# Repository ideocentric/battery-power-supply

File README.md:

# battery-power-supply
The purpose of this project is to have a rechargeable battery intended to be inside an enclosure for various synthesizer designs, however, it can be utilized for any purpose.

The motivation for this project was that I have not found an adequate solution.  There are a number of current solutions available, but the following limitations create issues for the overall design.

1.  Soldered on USB charging ports
2.  Soldered on power switch
3.  Soldered on power, charging and charge LEDs

Due to the above, they do not suite the usage inside of a project enclosure without desoldering these components and attaching wires in their place for panel mount switches, power and LEDs.

I have, however, found one solution that satisfied the above issues.  Unfortunately, these devices produced audible frequencies that prevented it being functional as a power supply for a sythesizer.

Due to the above conditions, I reached out to work with an engineer to help create the schematic and PCB layout for this purpose.  

The devise is intended to be used with 2 18650 batteries.  The JST connectors are provided to hook up the components such as the DC Barrel Jack for charging, 5v output for the device, Power switch and LEDs for Power, Charging and Charged status indicators.

The power supply should be 5v2a (or 5v3a).  Output is 5v1a.

I had the device manufactured at https://jlcpcb.com of which all components are normal stock items.

# Known Issues:
The current solution does not provide protection for low or short battery (perhaps this will be modified in a future version).

The status light output of the CN3302 IC is a little vague in it’s output as both lights appear to be on during charging.

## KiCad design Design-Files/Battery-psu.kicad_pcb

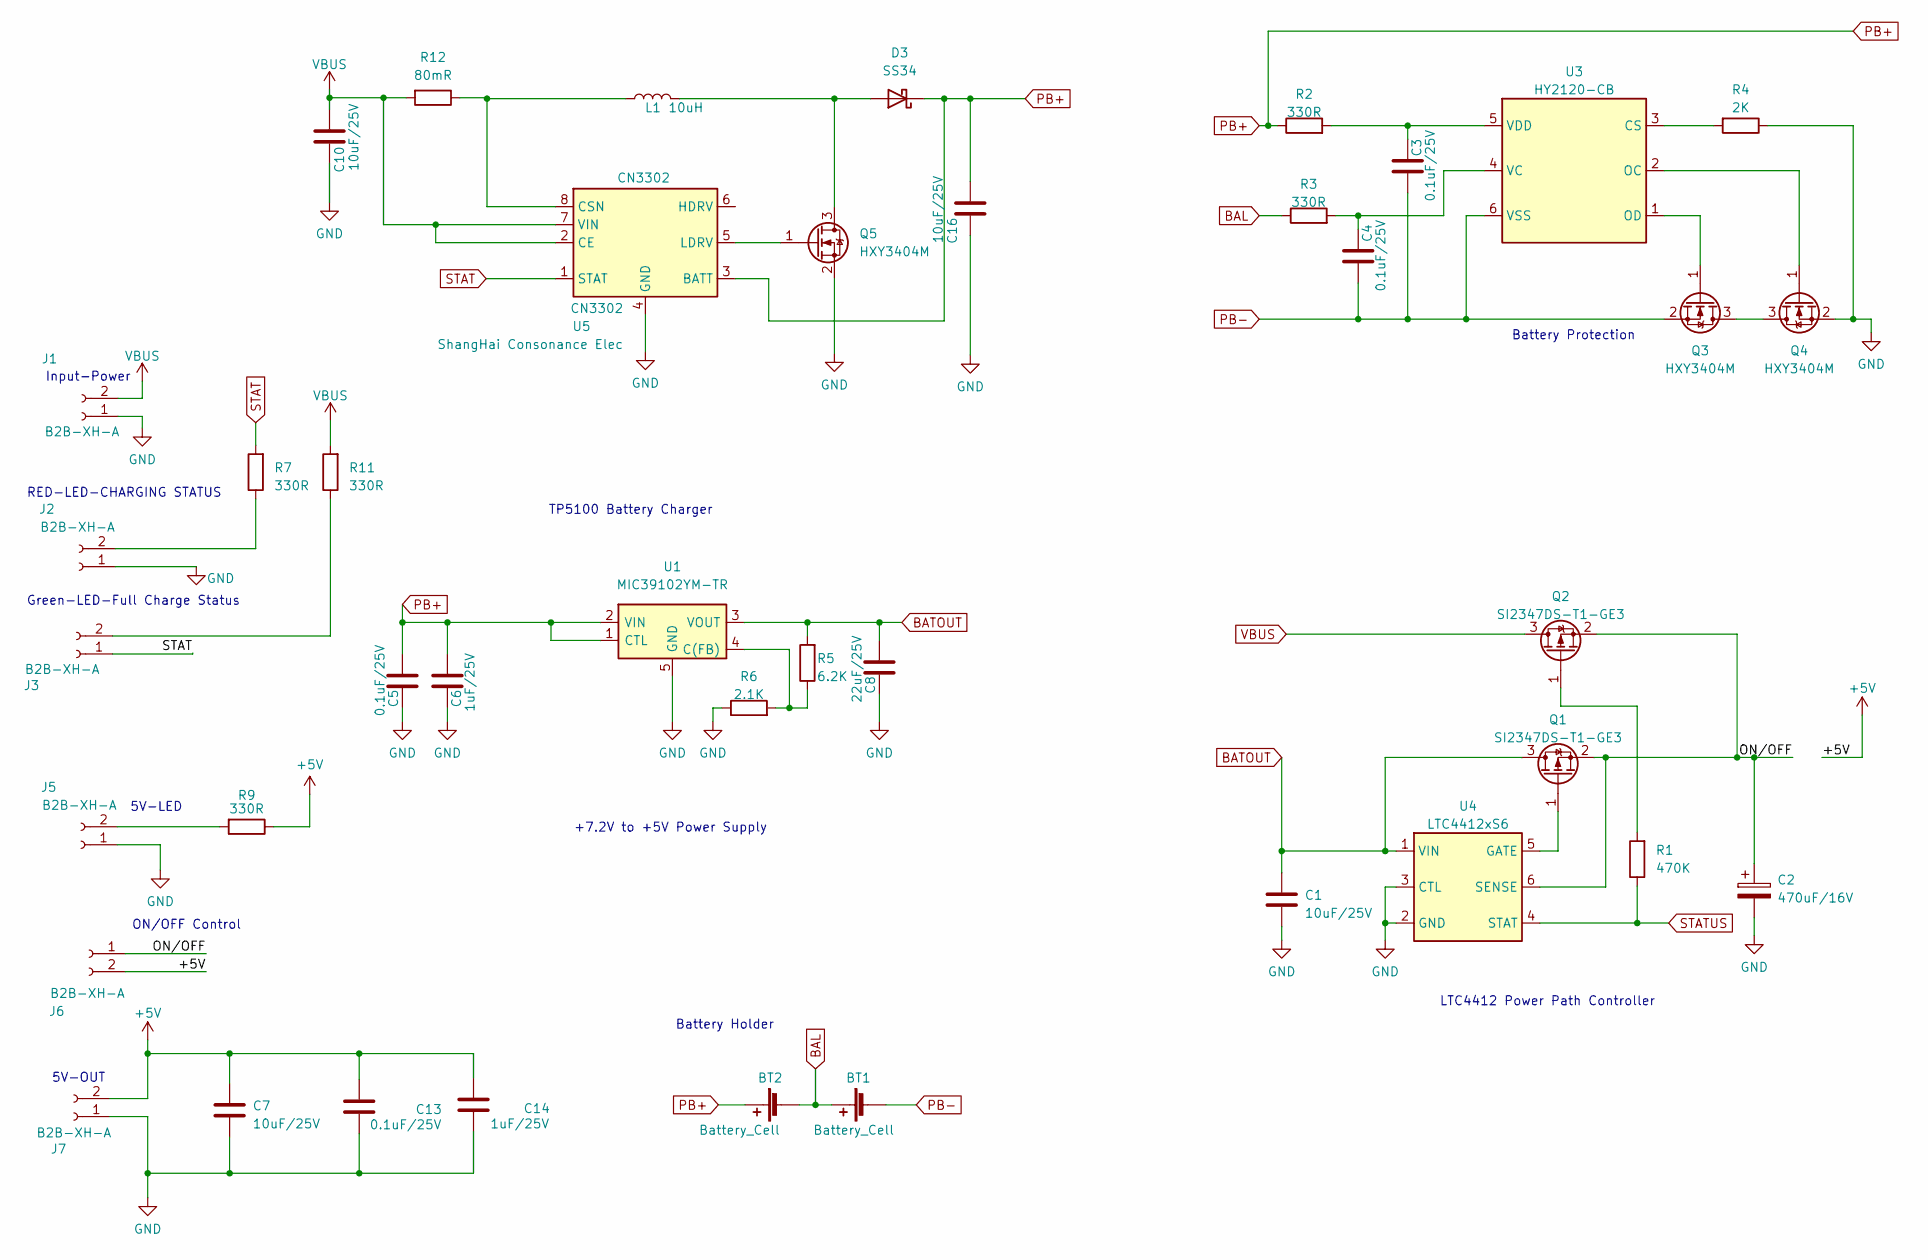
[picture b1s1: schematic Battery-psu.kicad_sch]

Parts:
BT1: Battery_Cell; BatteryHolder_MPD_BH-18650-PC2; LCSC-PN C19184083
BT2: Battery_Cell; BatteryHolder_MPD_BH-18650-PC2; LCSC PN C19184083
C1, C7, C10, C16: 10uF/25V; C_0603_1608Metric; LCSC PN C96446
C2: 470uF/16V; CP_Elec_6.3x7.7; LCSC PN C87858
C3, C4, C5, C13: 0.1uF/25V; C_0603_1608Metric; LCSC PN C83054
C6, C14: 1uF/25V; C_0603_1608Metric; LCSC PN C2857985
C8: 22uF/25V; C_0603_1608Metric; LCSC PN C602037
D3: SS34; D_SMA; LCSC PN C3011102
J1, J2, J3, J5, J6, J7: B2B-XH-A; JST_XH_B2B-XH-A_1x02_P2.50mm_Vertical; LCSC PN C158012
L1: 10uH; L_Wuerth_HCI-1040; LCSC PN C182194
Q1, Q2: SI2347DS-T1-GE3; SOT-23; LCSC PN C145002
Q3, Q4, Q5: HXY3404M; SOT-23; LCSC PN C2926128
R1: 470K; R_0603_1608Metric; LCSC PN C2907171
R2, R3, R7, R9, R11: 330R; R_0603_1608Metric; LCSC PN C2907152
R4: 2K; R_0603_1608Metric; LCSC PN C2907137
R5: 6.2K; R_0603_1608Metric; LCSC PN C2907054
R6: 2.1K; R_0603_1608Metric; LCSC PN C2907137
R12: 80mR; R_2512_6332Metric; LCSC PN C421509
U1: MIC39102YM-TR; SOIC-8_3.9x4.9mm_P1.27mm; LCSC PN C627993
U3: HY2120-CB; SOT-23-6; LCSC PN C116509
U4: LTC4412xS6; TSOT-23-6; LCSC PN C514442
U5: CN3302; SOIC-8_3.9x4.9mm_P1.27mm; LCSC PN C559039

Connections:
+5V: C7.1, C13.1, C14.1, J6.2, J7.2, R9.1
/ON/OFF: C2.1, J6.1, Q1.2 (S), Q2.2 (S), U4.6 (SENSE)
BAL: BT1.1 (+), BT2.2 (-), R3.1
BATOUT: C1.1, C8.1, Q1.3 (D), R5.2, U1.3 (VOUT), U4.1 (VIN)
GND: C1.2, C2.2, C5.2, C6.2, C7.2, C8.2, C10.2, C13.2, C14.2, C16.2, J1.1, J2.1, J5.1, J7.1, Q4.2 (S), Q5.2 (S), R4.1, R6.1, U1.5 (GND), U1.6 (GND), U1.7 (GND), U1.8 (GND), U4.2 (GND), U4.3 (CTL), U5.4 (GND)
unnamed: D3.2 (A), L1.2, Q5.3 (D)
unnamed: J2.2, R7.1
unnamed: J3.2, R11.1
unnamed: J5.2, R9.2
unnamed: Q1.1 (G), U4.5 (GATE)
unnamed: Q2.1 (G), R1.2
unnamed: Q3.3 (D), Q4.3 (D)
unnamed: Q3.1 (G), U3.1 (OD)
unnamed: Q4.1 (G), U3.2 (OC)
unnamed: Q5.1 (G), U5.5 (LDRV)
unnamed: R5.1, R6.2, U1.4 (C(FB))
unnamed: R4.2, U3.3 (CS)
unnamed: C4.1, R3.2, U3.4 (VC)
unnamed: C3.1, R2.2, U3.5 (VDD)
unnamed: L1.1, R12.1, U5.8 (CSN)
PB+: BT2.1 (+), C5.1, C6.1, C16.1, D3.1 (K), R2.1, U1.1 (CTL), U1.2 (VIN), U5.3 (BATT)
PB-: BT1.2 (-), C3.2, C4.2, Q3.2 (S), U3.6 (VSS)
STAT: J3.1, R7.2, U5.1 (STAT)
STATUS: R1.1, U4.4 (STAT)
VBUS: C10.1, J1.2, Q2.3 (D), R11.2, R12.2, U5.2 (CE), U5.7 (VIN)

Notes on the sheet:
ON/OFF Control
Battery Holder
5V-LED
+7.2V to +5V Power Supply
5V-OUT
LTC4412 Power Path Controller
RED-LED-CHARGING STATUS
Battery Protection
TP5100 Battery Charger
Green-LED-Full Charge Status
Input-Power

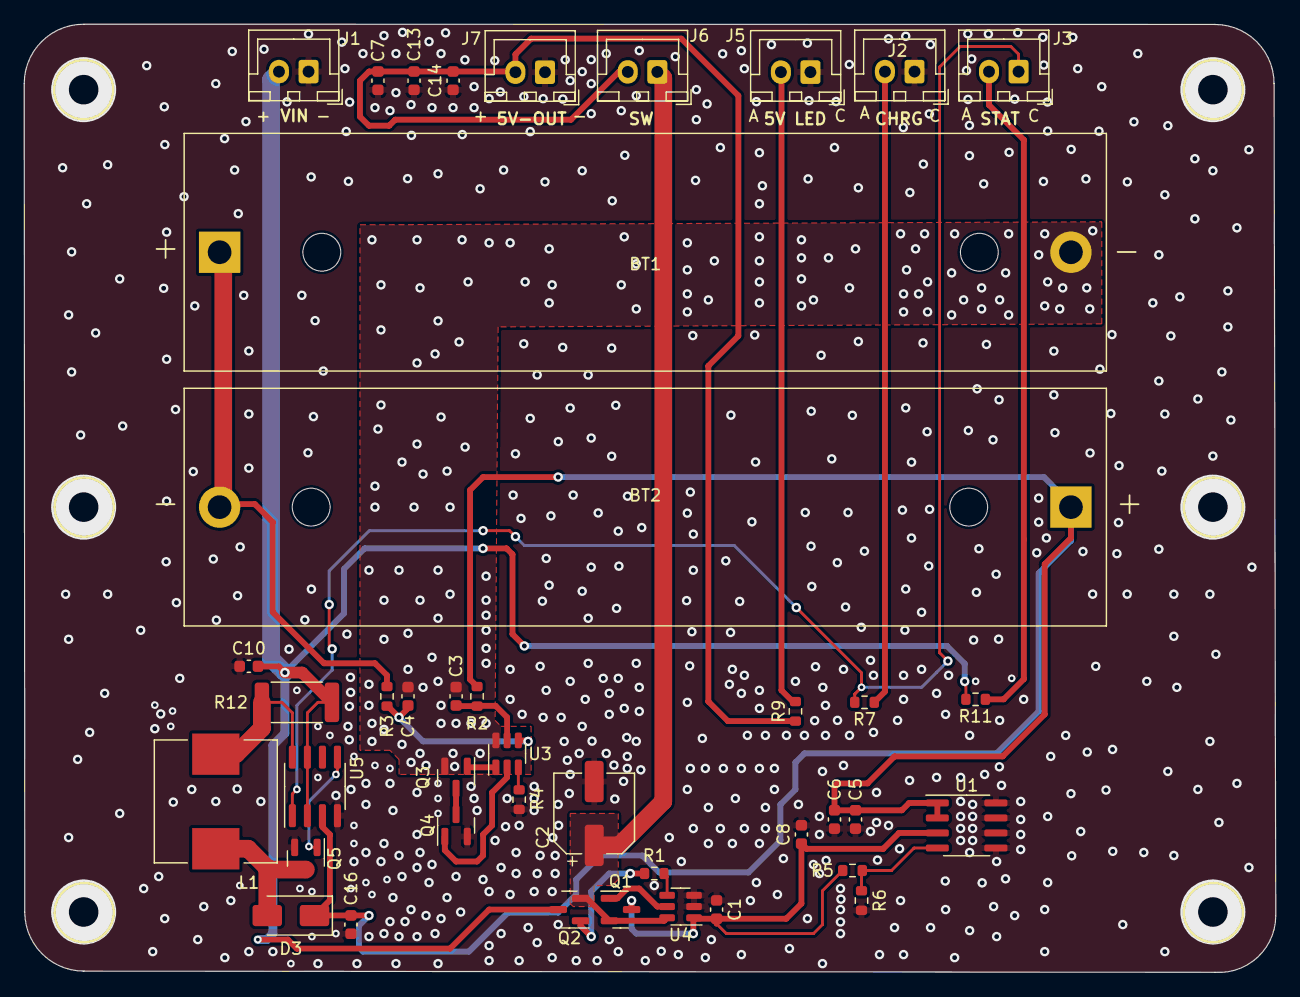
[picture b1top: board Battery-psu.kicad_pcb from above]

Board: 2 copper layers, 105.8 x 80.2 mm, 41 parts (0 on the bottom side), 25 nets.

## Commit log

2024-04-30 Update .gitignore
    Updated gitignore for MacOS and Windows .turd files
2024-04-30 Update .gitignore
    Added linux ignores
2024-04-30 initial file commit
2024-04-30 added photo
